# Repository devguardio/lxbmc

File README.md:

# lxbmc

board managment controller for the solid-run honeycomb arm server

 - screws into a 2.5' drive bay
 - controlls power on.off
 - usb for virtual ethernet and disk
 - access the cpus local serial terminal remotely

# setup

after installing ubuntu with the usual usbboot thing:

    echo 'dtoverlay=dwc2,dr_mode=peripheral' >> /boot/firmware/config.txt

    systemctl stop serial-getty@ttyS0.service
    systemctl mask serial-getty@ttyS0.service

    systemctl stop systemd-resolved
    systemctl disable systemd-resolved
    rm /etc/resolv.conf
    echo nameserver 8.8.8.8 >  /etc/resolv.conf
    apt install dnsmasq
    systemctl stop dnsmasq
    systemctl disable dnsmasq

then install starfeldt bmc and config as:

    [power]
    switch='gpio5'

    [serial]
    device='/dev/ttyS0'

    [usb]

or if you're not a devguard customer maybe look at pikvm.org for a free alternative

# fan

https://github.com/neg2led/cm4io-fan

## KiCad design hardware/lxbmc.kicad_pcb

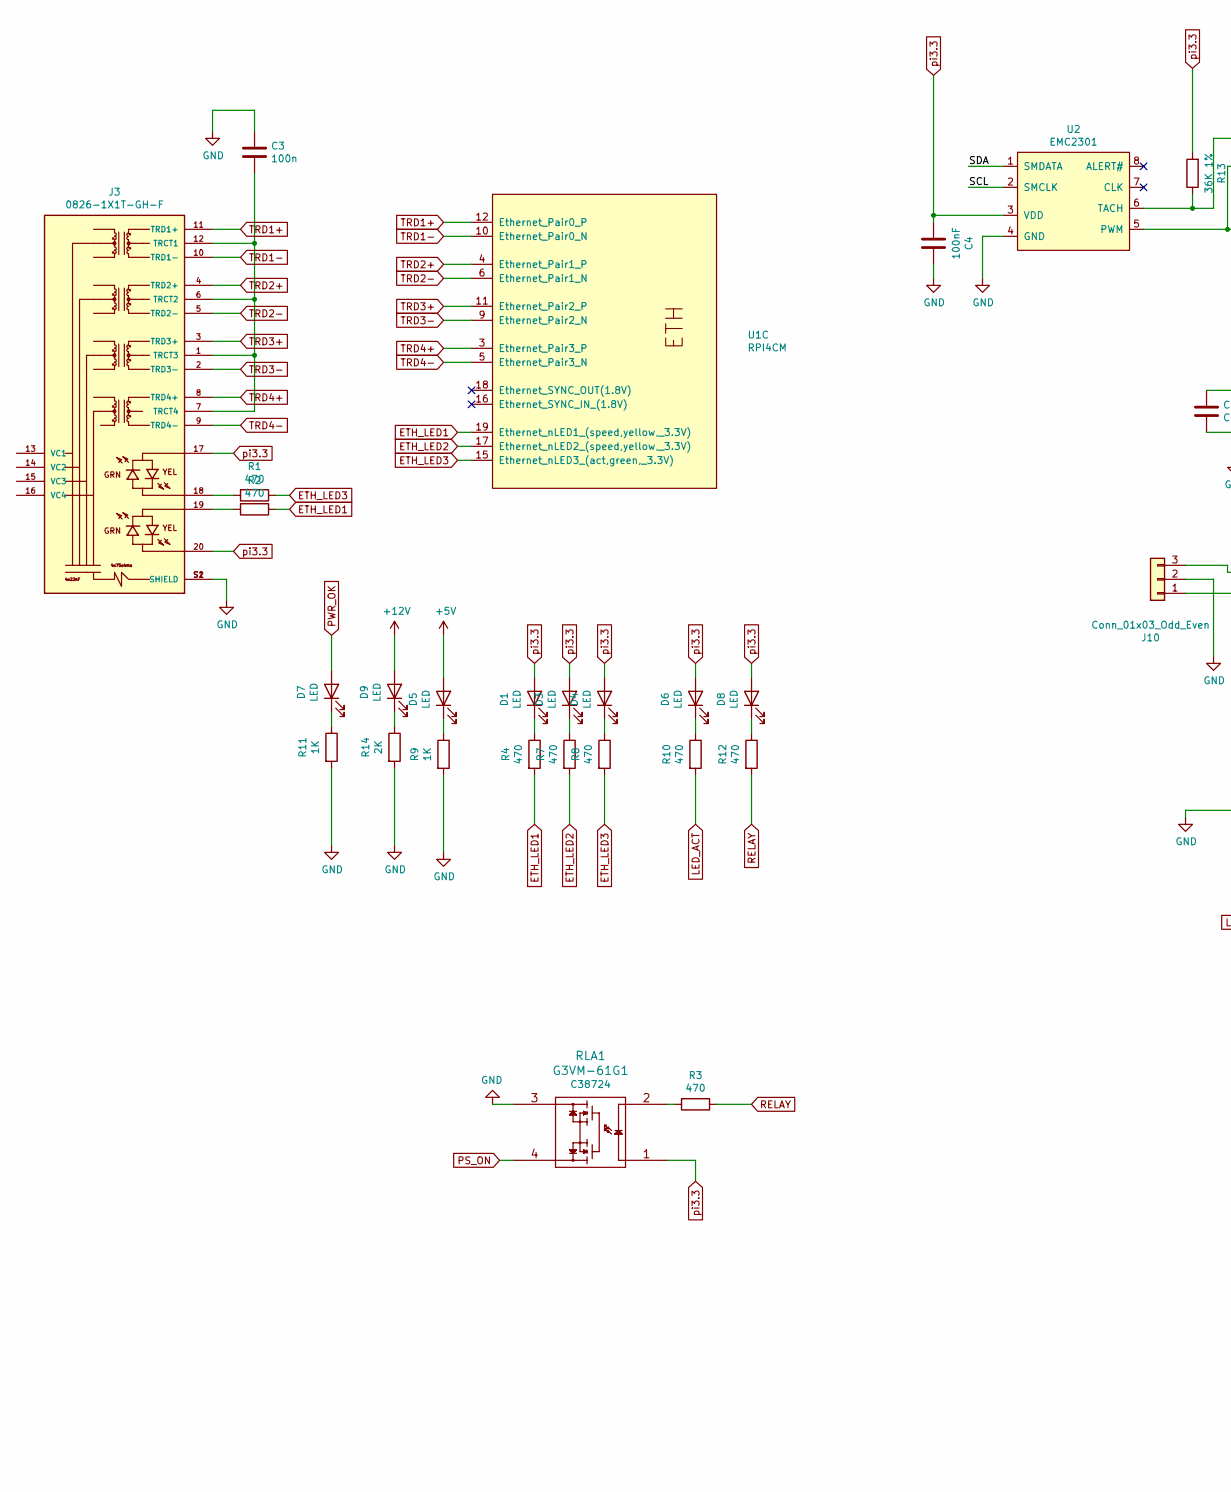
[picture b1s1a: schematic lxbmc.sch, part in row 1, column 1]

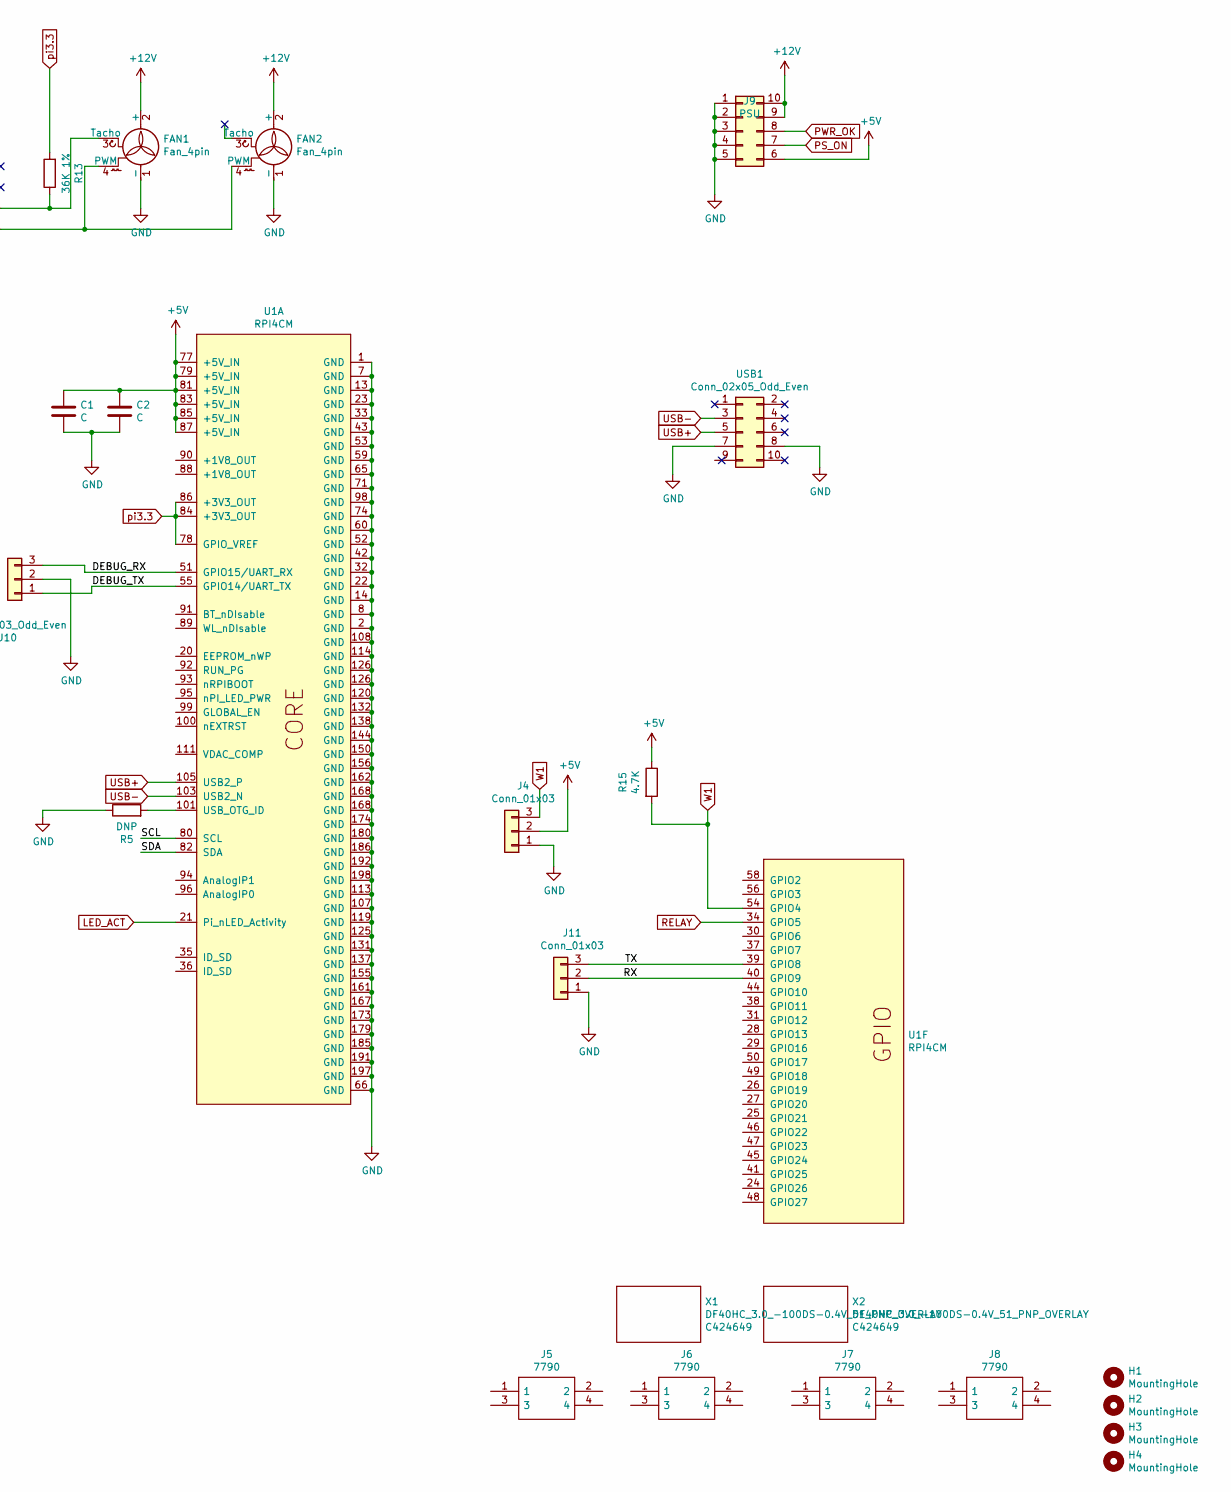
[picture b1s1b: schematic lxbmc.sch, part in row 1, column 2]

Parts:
C1: C; C_0603_1608Metric; JLC# C14858
C2: C; C_0805_2012Metric; JLC# C15850
C3: 100n; C_0603_1608Metric
C4: 100nF; C_0603_1608Metric
D1, D6, D7, D8: LED; LED_0402_1005Metric; JLC# C130723
D3: LED; LED_0402_1005Metric; JLC# C130721
D4: LED; LED_0402_1005Metric; JLC# C688877
D5, D9: LED; LED_0402_1005Metric; JLC# C397045
FAN1, FAN2: Fan_4pin; Molex_KK-254_AE-6410-04A_1x04_P2.54mm_Vertical
H1, H2, H3, H4: MountingHole; MountingHole_3.2mm_M3_DIN965_Mask
J3: 0826-1X1T-GH-F; BEL_0826-1X1T-GH-F
J4, J11: Conn_01x03; Molex_KK-254_AE-6410-03A_1x03_P2.54mm_Vertical
J5, J6, J7, J8: 7790; Manufacturer_Part_Number 7790; Mouser Part Number 534-7790
J9: PSU; Molex_Mini-Fit_Jr_5566-10A_2x05_P4.20mm_Vertical
J10: Conn_01x03_Odd_Even; PinHeader_1x03_P2.54mm_Vertical
R1, R2, R3, R4, R7, R8, R10, R12: 470; R_0402_1005Metric; LCSC# C25117
R5: DNP; R_0402_1005Metric
R9, R11: 1K; R_0402_1005Metric
R13: 36K 1%; R_0402_1005Metric; JLC# C43676
R14: 2K; R_0402_1005Metric
R15: 4.7K; R_0402_1005Metric; JLC# C25900
RLA1: G3VM-61G1; G3VM-SOP; LCSC# C38724
U1: RPI4CM; rpi_cm4
U2: EMC2301; MSOP-8_3x3mm_P0.65mm; LCSC# C148036
USB1: Conn_02x05_Odd_Even; PinHeader_2x05_P2.54mm_Vertical
X1, X2: DF40HC_3.0_-100DS-0.4V_51_PNP_OVERLAY; HRS_DF40HC(3.0)-100DS-0.4V(58)_PNP_OVERLAY; Manufacturer_Part_Number DF40HC(3.0)-100DS-0.4V(51; Mouser Part Number 798-DF40HC30100DS451

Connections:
+5V: C1.1, C2.1, D5.2 (A), J4.2, J9.6, R15.1, U1.77 (+5V_IN), U1.79 (+5V_IN), U1.81 (+5V_IN), U1.83 (+5V_IN), U1.85 (+5V_IN), U1.87 (+5V_IN)
+12V: D9.2 (A), FAN1.2 (+), FAN2.2 (+), J9.9, J9.10
/DEBUG_RX: J10.3, U1.51 (GPIO15/UART_RX)
/DEBUG_TX: J10.1, U1.55 (GPIO14/UART_TX)
/RX: J11.2, U1.40 (GPIO9)
/SCL: U1.80 (SCL), U2.2 (SMCLK)
/SDA: U1.82 (SDA), U2.1 (SMDATA)
/TX: J11.3, U1.39 (GPIO8)
ETH_LED1: R2.1, R4.2, U1.19 (Ethernet_nLED1_(speed,yellow,_3.3V))
ETH_LED2: R7.2, U1.17 (Ethernet_nLED2_(speed,yellow,_3.3V))
ETH_LED3: R1.1, R8.2, U1.15 (Ethernet_nLED3_(act,green,_3.3V))
GND: C1.2, C2.2, C3.1, C4.2, FAN1.1 (-), FAN2.1 (-), J3.S1 (SHIELD), J3.S2 (SHIELD), J4.1, J9.1, J9.2, J9.3, J9.4, J9.5, J10.2, J11.1, R5.1, R9.2, R11.2, R14.2, RLA1.3, U1.1 (GND), U1.2 (GND), U1.7 (GND), U1.8 (GND), U1.13 (GND), U1.14 (GND), U1.22 (GND), U1.23 (GND), U1.32 (GND), U1.33 (GND), U1.42 (GND), U1.43 (GND), U1.52 (GND), U1.53 (GND), U1.59 (GND), U1.60 (GND), U1.65 (GND), U1.66 (GND), U1.71 (GND), U1.74 (GND), U1.98 (GND), U1.107 (GND), U1.108 (GND), U1.113 (GND), U1.114 (GND), U1.119 (GND), U1.120 (GND), U1.125 (GND), U1.126 (GND), U1.131 (GND), U1.132 (GND), U1.137 (GND), U1.138 (GND), U1.144 (GND), U1.150 (GND), U1.155 (GND), U1.156 (GND), U1.161 (GND), U1.162 (GND), U1.167 (GND), U1.168 (GND), U1.173 (GND), U1.174 (GND), U1.179 (GND), U1.180 (GND), U1.185 (GND), U1.186 (GND), U1.191 (GND), U1.192 (GND), U1.197 (GND), U1.198 (GND), U2.4 (GND), USB1.7, USB1.8
LED_ACT: R10.2, U1.21 (Pi_nLED_Activity)
unnamed: C3.2, J3.1 (TRCT3), J3.6 (TRCT2), J3.7 (TRCT4), J3.12 (TRCT1)
unnamed: D1.1 (K), R4.1
unnamed: D3.1 (K), R7.1
unnamed: D4.1 (K), R8.1
unnamed: D5.1 (K), R9.1
unnamed: D6.1 (K), R10.1
unnamed: D7.1 (K), R11.1
unnamed: D8.1 (K), R12.1
unnamed: D9.1 (K), R14.1
unnamed: FAN1.3 (Tacho), R13.1, U2.6 (TACH)
unnamed: FAN1.4 (PWM), FAN2.4 (PWM), U2.5 (PWM)
unnamed: J3.18, R1.2
unnamed: J3.19, R2.2
unnamed: R3.2, RLA1.2
unnamed: R5.2, U1.101 (USB_OTG_ID)
PS_ON: J9.7, RLA1.4
PWR_OK: D7.2 (A), J9.8
RELAY: R3.1, R12.2, U1.34 (GPIO5)
TRD1+: J3.11 (TRD1+), U1.12 (Ethernet_Pair0_P)
TRD1-: J3.10 (TRD1-), U1.10 (Ethernet_Pair0_N)
TRD2+: J3.4 (TRD2+), U1.4 (Ethernet_Pair1_P)
TRD2-: J3.5 (TRD2-), U1.6 (Ethernet_Pair1_N)
TRD3+: J3.3 (TRD3+), U1.11 (Ethernet_Pair2_P)
TRD3-: J3.2 (TRD3-), U1.9 (Ethernet_Pair2_N)
TRD4+: J3.8 (TRD4+), U1.3 (Ethernet_Pair3_P)
TRD4-: J3.9 (TRD4-), U1.5 (Ethernet_Pair3_N)
USB+: U1.105 (USB2_P), USB1.5
USB-: U1.103 (USB2_N), USB1.3
W1: J4.3, R15.2, U1.54 (GPIO4)
pi3.3: C4.1, D1.2 (A), D3.2 (A), D4.2 (A), D6.2 (A), D8.2 (A), J3.17, J3.20, R13.2, RLA1.1, U1.78 (GPIO_VREF), U1.84 (+3V3_OUT), U1.86 (+3V3_OUT), U2.3 (VDD)

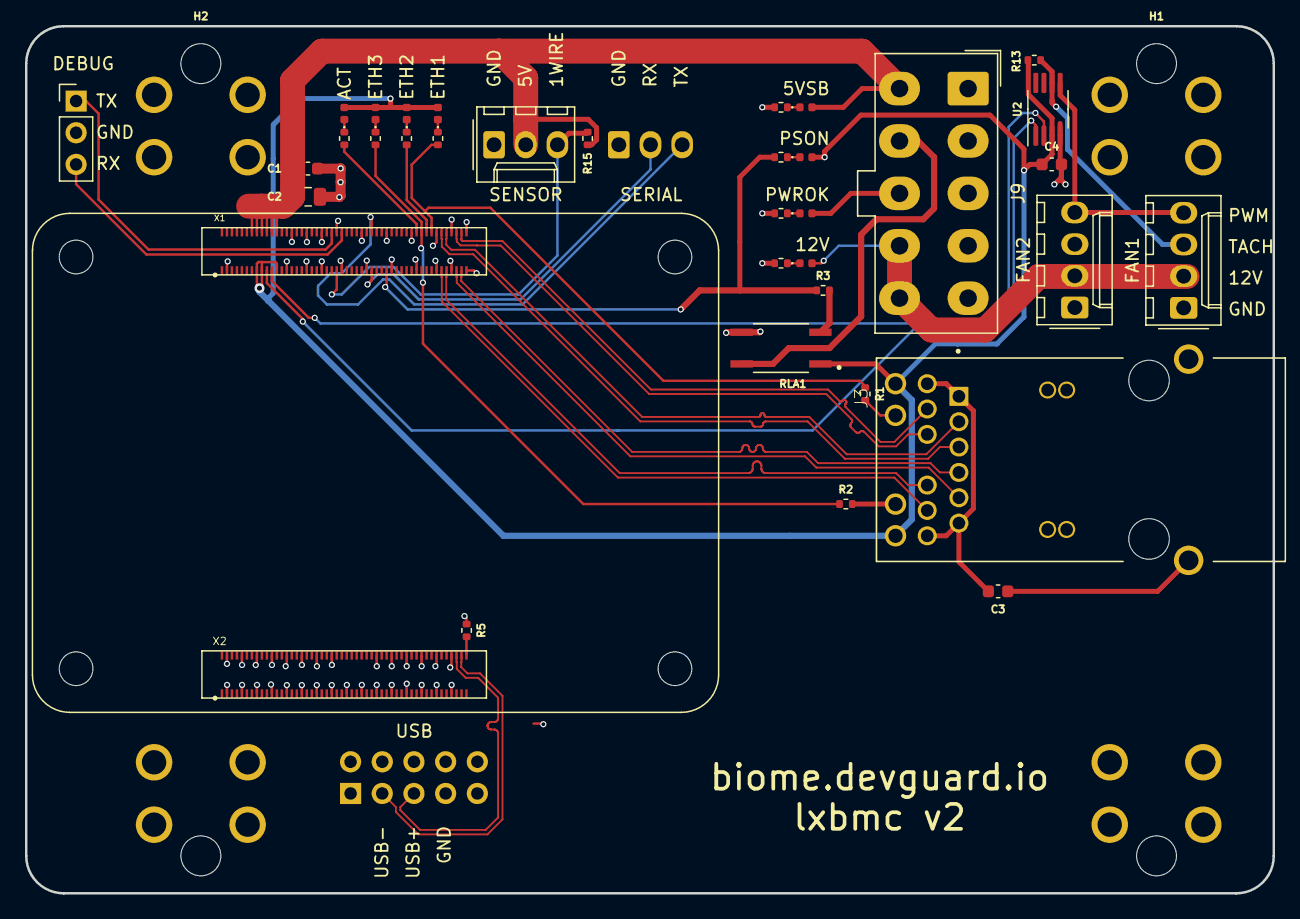
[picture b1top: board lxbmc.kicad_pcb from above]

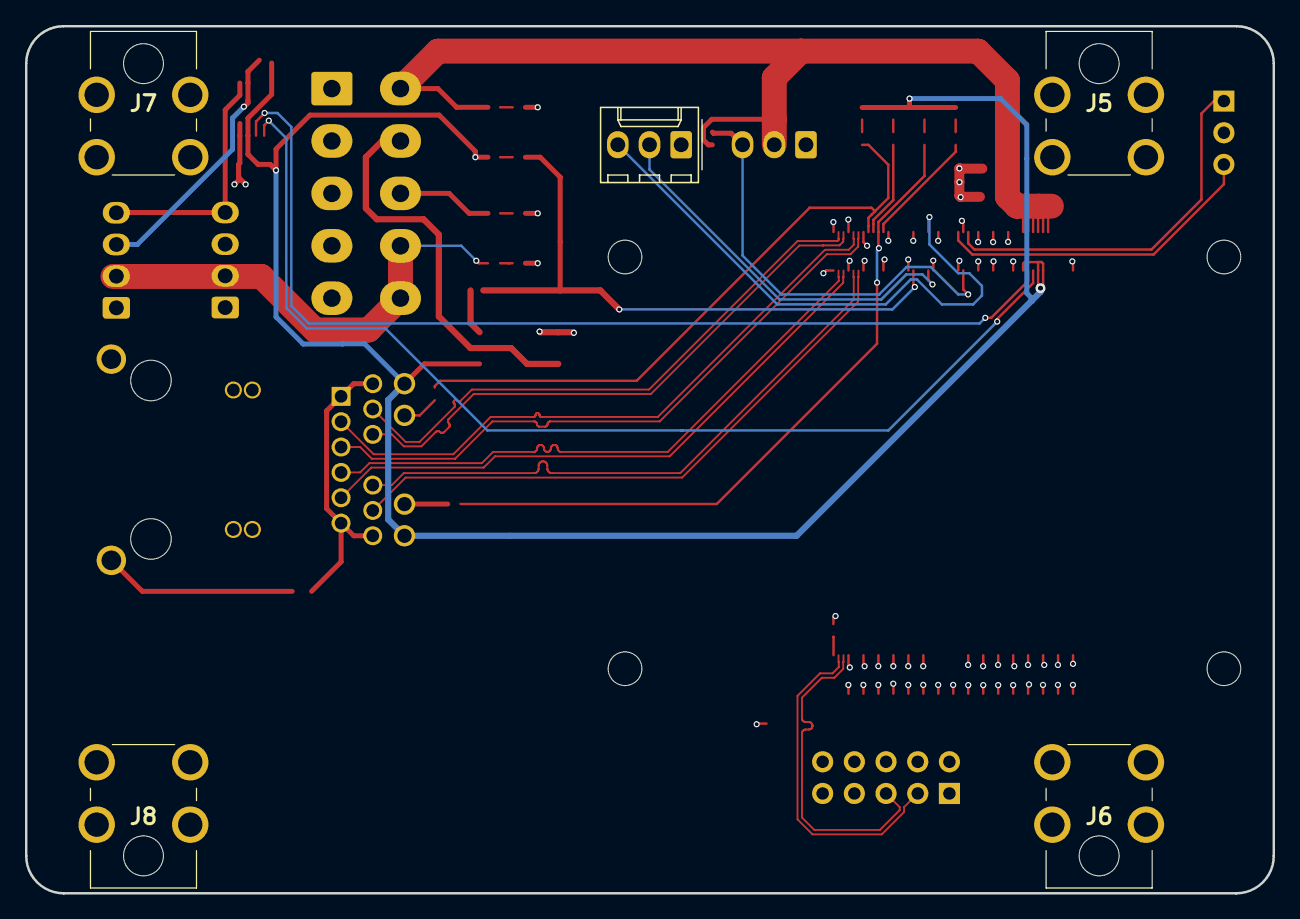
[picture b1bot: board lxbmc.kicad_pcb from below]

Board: 4 copper layers, 100.0 x 69.5 mm, 47 parts (5 on the bottom side), 43 nets.

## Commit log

2021-08-05 init
